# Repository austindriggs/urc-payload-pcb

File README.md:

# Payload PCB at WVU for Mars Society's University Rover Challenge (URC)

## SUMMARY

The Payload PCB serves as an all-purpose control and interface board that contains the Raspberry Pi Pico (RP2040) designed to manage mission-critical sensors and electronics and communicate that information through its Micro USB connector to the LattePanda Sigma SBC.

Learn how to [contribute](CONTRIBUTING.md) (with pictures) to this project.

## FEATURES

- Resettable PTC fuse and reverse voltage protection on +12V Molex Micro-Fit input.
- LTC2990 Quad I2C Voltage, Current, and Temperature Monitor.
- Traco TSR 2 Series +5V and +3V3 regulators: 96% eff, no heat sink required, built in filter caps, and short circuit protection.
- Outputs +12V, +5V, and +3V3 on Molex Micro-Fit.
- Status and error LEDs.
- Connections for both the Pico and an external device to CAN bus.
- 4x STEMMA QT / QWIIC connectors for COTS modules and peripherals.
- 2x custom expansion modules on two 6 pin 0.1" connectors each.
- 4x servo (PWM) outputs on Molex PicoBlades.
- 3x analog inputs on Molex Picoblades.
- 2x digital outputs for relays.
- 2x digital inputs (active-low) for limit switches on manipulator linear rail.
- Micro USB port with soft start to connect to Seeeduino XIAO on manipulator.

## DESIGN

<!--
### SCHEMATIC

TODO

### LAYOUT
--->

<!--
### MODEL

TODO
--->

## DEIMOS (ROVER) AND PHOBOS (DRONE) FOR 2026

Click the image below to watch the System Acceptance Review (SAR) on YouTube:  

## LICENSE

This project is published under the MIT [license](LICENSE).

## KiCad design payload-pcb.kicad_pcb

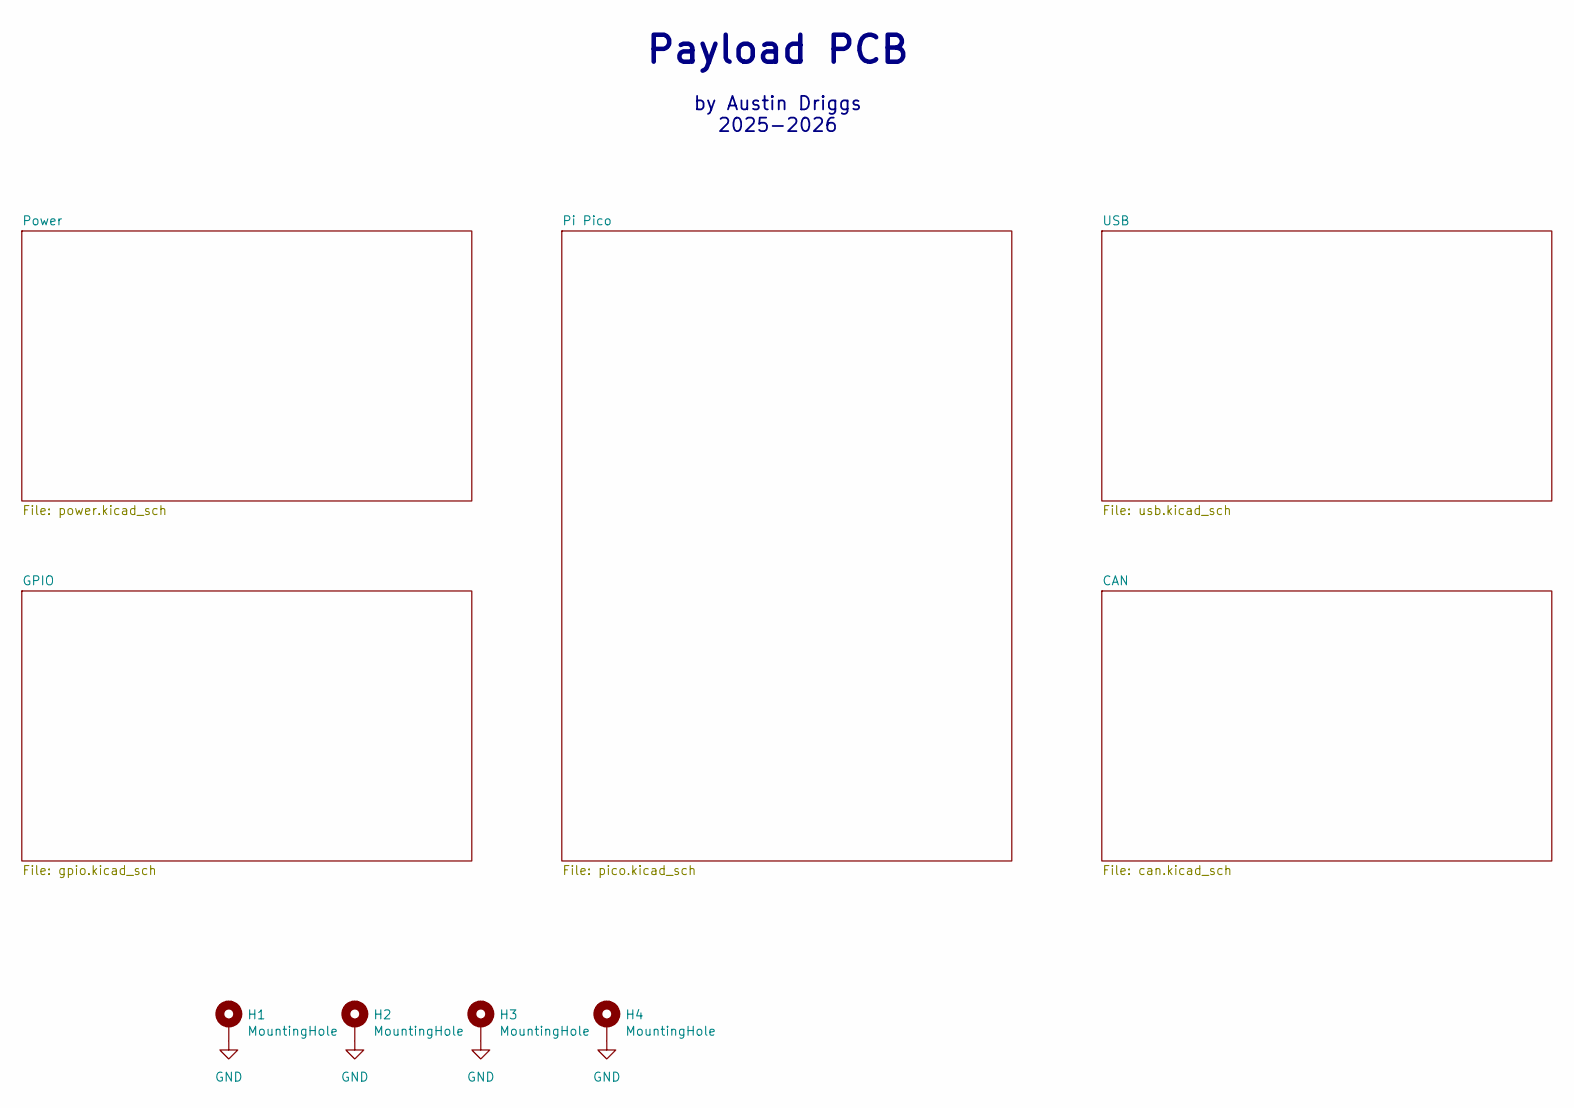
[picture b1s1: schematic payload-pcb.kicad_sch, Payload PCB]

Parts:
H1, H2, H3, H4: MountingHole; MountingHole_3.2mm_M3_DIN965_Pad

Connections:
GND: H1.1, H2.1, H3.1, H4.1; also elsewhere on the board

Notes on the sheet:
Payload PCB
by Austin Driggs 2025-2026

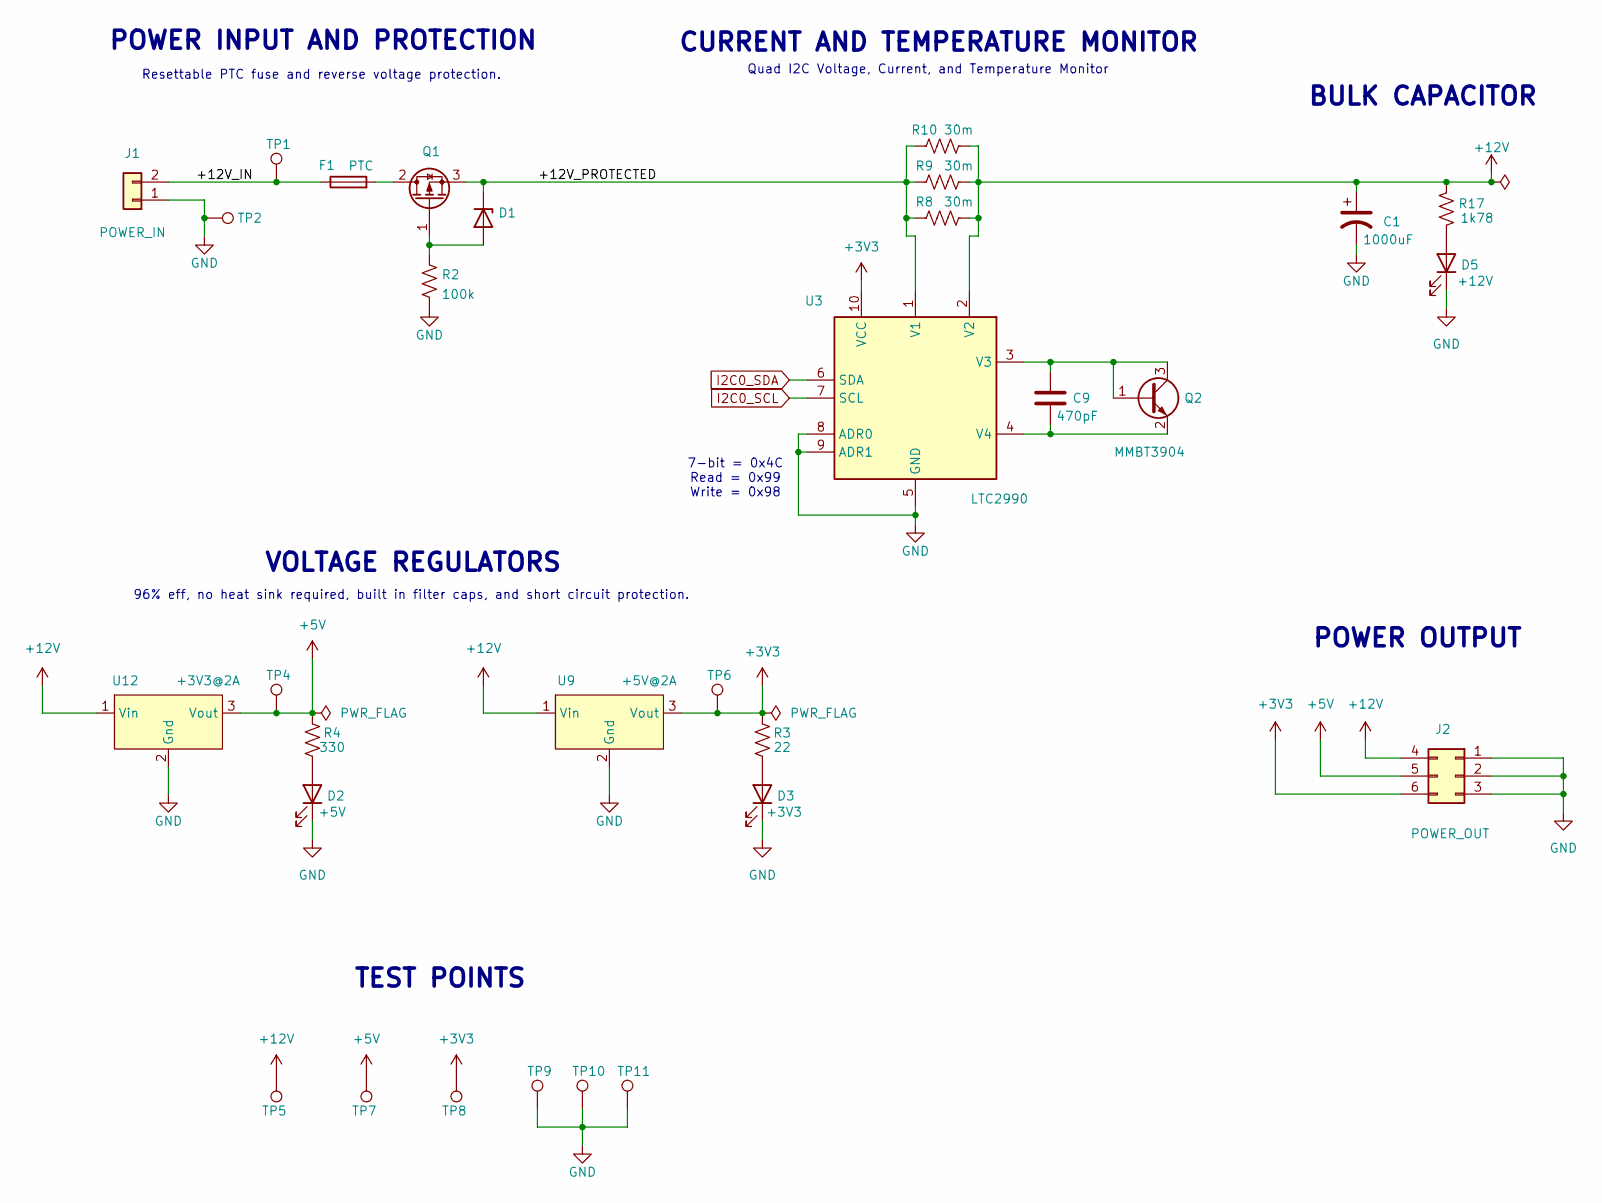
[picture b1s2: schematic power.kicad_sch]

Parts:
C1: 1000uF; CP_Radial_D10.0mm_P5.00mm; Manufacturer Part Number UVR1E102MPD
C9: 470pF; C_0603_1608Metric_Pad1.08x0.95mm_HandSolder; Manufacturer Part Number C0603C471K5RACTU
D1: BZT52C10-TP; D_SOD-123; Manufacturer Part Number BZT52C10-TP
D2: +5V; LED_0805_2012Metric_Pad1.15x1.40mm_HandSolder; Manufacturer Part Number 150080GS75000
D3: +3V3; LED_0805_2012Metric_Pad1.15x1.40mm_HandSolder; Manufacturer Part Number 150080GS75000
D5: +12V; LED_0805_2012Metric_Pad1.15x1.40mm_HandSolder; Manufacturer Part Number 150080GS75000
F1: PTC; Fuse_1210_3225Metric; Manufacturer Part Number 1210L150/16WR
J1: POWER_IN; Molex_Micro-Fit_3.0_43045-0200_2x01_P3.00mm_Horizontal; Manufacturer Part Number 0430450200
J2: POWER_OUT; Molex_Micro-Fit_3.0_43045-0600_2x03_P3.00mm_Horizontal; Manufacturer Part Number 0430450602
Q1: SUD50P10-43L-GE3; TO-252-2; Manufacturer Part Number SUD50P10-43L-GE3
Q2: MMBT3904; SOT-23; Manufacturer Part Number MMBT3904LT1G
R2: 100k; R_0603_1608Metric_Pad0.98x0.95mm_HandSolder; Manufacturer Part Number RMCF0603FT100K
R3: 22; R_0603_1608Metric_Pad0.98x0.95mm_HandSolder; Manufacturer Part Number RNCP0603FTD22R1
R4: 330; R_0603_1608Metric_Pad0.98x0.95mm_HandSolder; Manufacturer Part Number RNCP0603FTD332R
R8, R9, R10: 30m; R_1206_3216Metric_Pad1.30x1.75mm_HandSolder; Manufacturer Part Number CSR1206FT30L0
R17: 1k78; R_0603_1608Metric_Pad0.98x0.95mm_HandSolder; Manufacturer Part Number RNCP0603FTD1K78
TP1: +12V_IN; TestPoint_Pad_D2.0mm
TP2, TP9, TP10, TP11: GND; TestPoint_Pad_D2.0mm
TP4, TP7: +5V; TestPoint_Pad_D2.0mm
TP5: +12V; TestPoint_Pad_D2.0mm
TP6, TP8: +3V3; TestPoint_Pad_D2.0mm
U3: LTC2990; MSOP-10_3x3mm_P0.5mm; Manufacturer Part Number LTC2990IMS#TRPBF
U9: +5V@2A; TSR_2-24xx; Manufacturer Part Number TSR 2-2450
U12: +3V3@2A; TSR_2-24xx; Manufacturer Part Number TSR 2-2433

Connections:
+3V3: J2.6, R3.2, TP6.1, TP8.1, U3.10 (VCC), U9.3 (Vout); also elsewhere on the board
+5V: J2.5, R4.2, TP4.1, TP7.1, U12.3 (Vout); also elsewhere on the board
+12V: C1.1, J2.4, R8.2, R9.2, R10.2, R17.2, TP5.1, U3.2 (V2), U9.1 (Vin), U12.1 (Vin)
/Power/+12V_IN: F1.1, J1.2, TP1.1
/Power/+12V_PROTECTED: D1.1 (K), Q1.3 (S), R8.1, R9.1, R10.1, U3.1 (V1)
GND: C1.2, D2.1 (K), D3.1 (K), D5.1 (K), J1.1, J2.1, J2.2, J2.3, R2.2, TP2.1, TP9.1, TP10.1, TP11.1, U3.5 (GND), U3.8 (ADR0), U3.9 (ADR1), U9.2 (Gnd), U12.2 (Gnd); also elsewhere on the board
I2C0_SCL: U3.7 (SCL); also elsewhere on the board
I2C0_SDA: U3.6 (SDA); also elsewhere on the board
unnamed: D1.2 (A), Q1.1 (G), R2.1
unnamed: D2.2 (A), R4.1
unnamed: D3.2 (A), R3.1
unnamed: D5.2 (A), R17.1
unnamed: F1.2, Q1.2 (D)
unnamed: C9.2, Q2.1 (B), Q2.3 (C), U3.3 (V3)
unnamed: C9.1, Q2.2 (E), U3.4 (V4)

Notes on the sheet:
96% eff, no heat sink required, built in filter caps, and short circuit protection.
CURRENT AND TEMPERATURE MONITOR
BULK CAPACITOR
VOLTAGE REGULATORS
Resettable PTC fuse and reverse voltage protection.
TEST POINTS
POWER OUTPUT
7-bit = 0x4C Read = 0x99 Write = 0x98
POWER INPUT AND PROTECTION
Quad I2C Voltage, Current, and Temperature Monitor

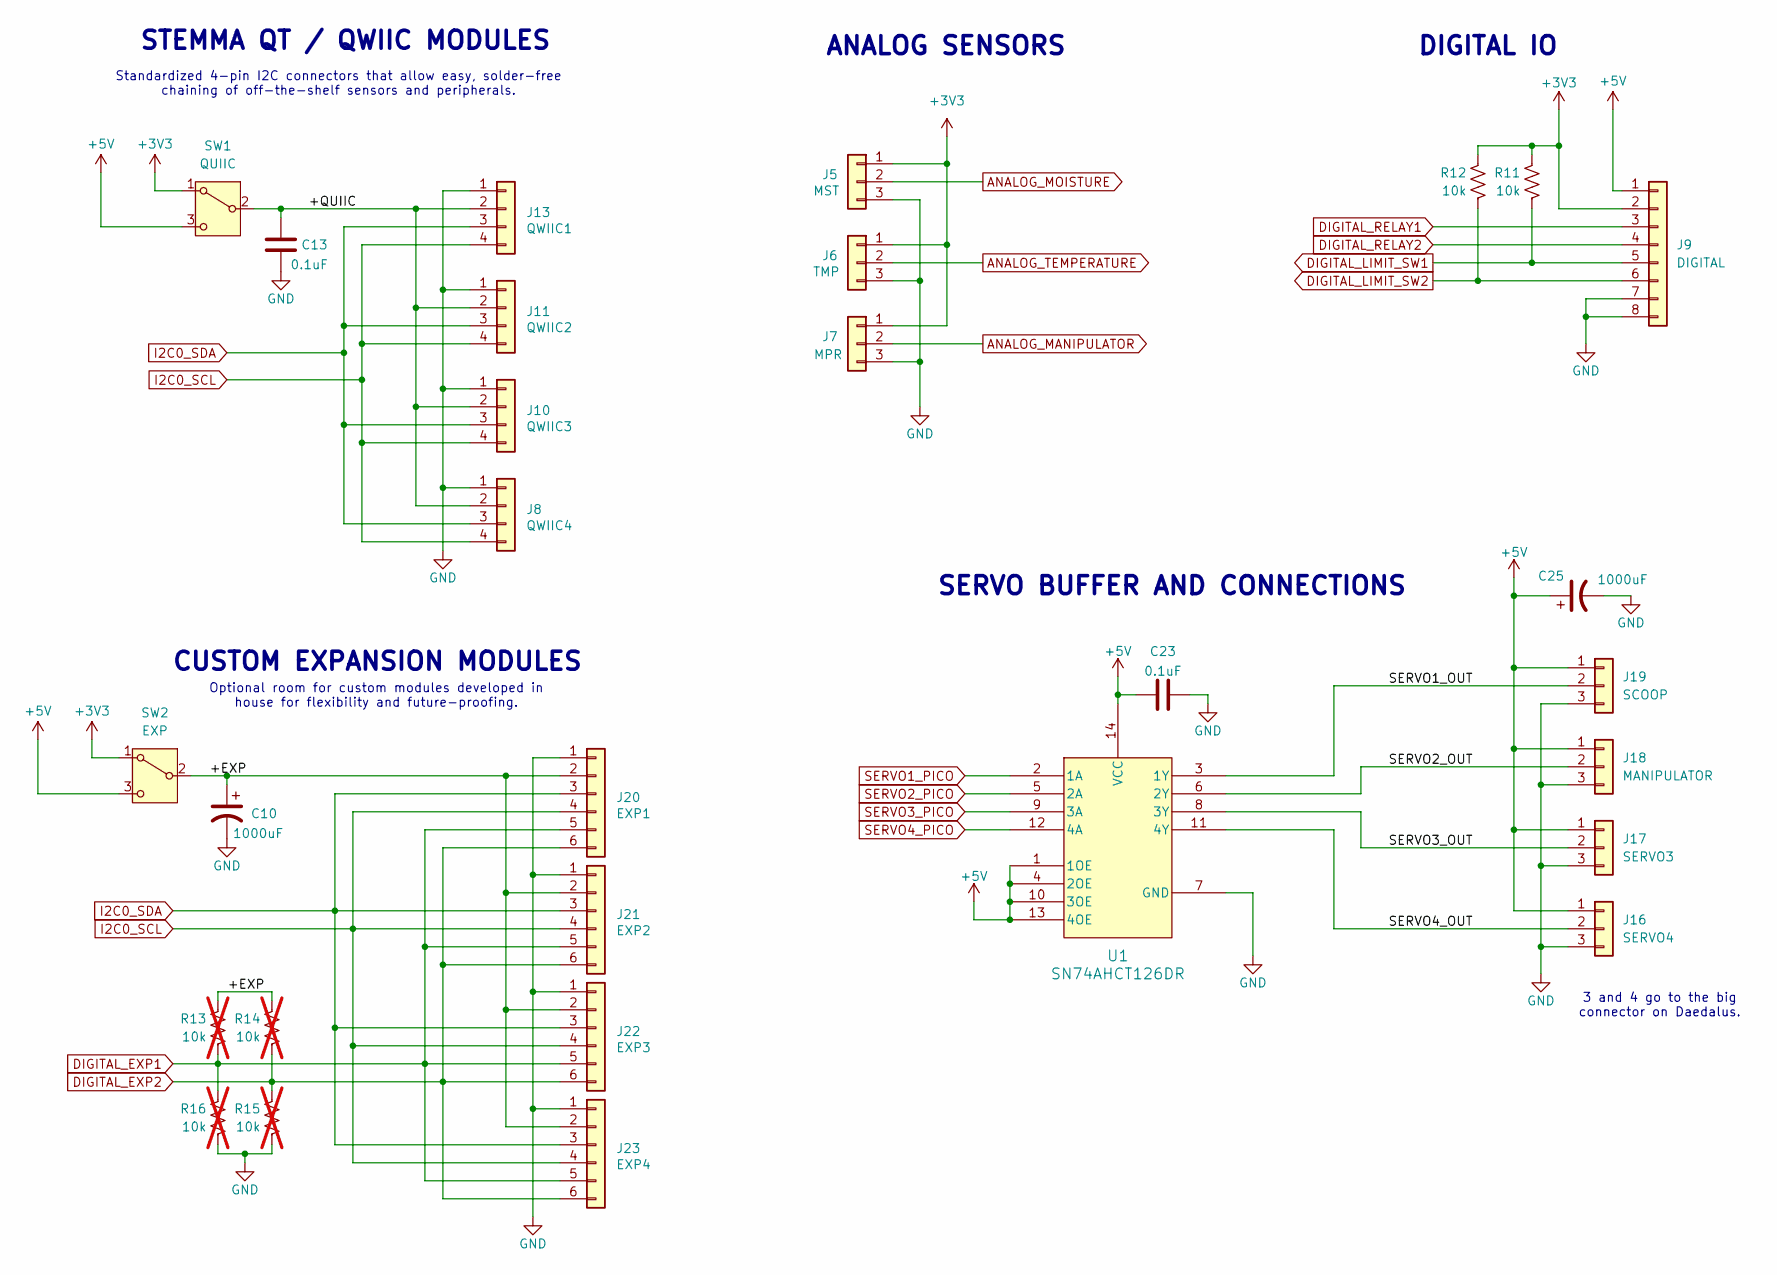
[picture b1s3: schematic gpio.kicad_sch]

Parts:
C10, C25: 1000uF; CP_Radial_D10.0mm_P5.00mm; Manufacturer Part Number UVR1E102MPD
C13, C23: 0.1uF; C_1206_3216Metric_Pad1.33x1.80mm_HandSolder; Manufacturer Part Number C1206C104J5RACTU
J5: MST; Molex_PicoBlade_53047-0310_1x03_P1.25mm_Vertical; Manufacturer Part Number 0530470310
J6: TMP; Molex_PicoBlade_53047-0310_1x03_P1.25mm_Vertical; Manufacturer Part Number 0530470310
J7: MPR; Molex_PicoBlade_53047-0310_1x03_P1.25mm_Vertical; Manufacturer Part Number 0530470310
J8: QWIIC4; JST_GH_BM04B-GHS-TBT_1x04-1MP_P1.25mm_Vertical; Manufacturer Part Number SM04B-GHS-TB
J9: DIGITAL; Molex_PicoBlade_53047-0810_1x08_P1.25mm_Vertical; Manufacturer Part Number 0530470810
J10: QWIIC3; JST_GH_BM04B-GHS-TBT_1x04-1MP_P1.25mm_Vertical; Manufacturer Part Number SM04B-GHS-TB
J11: QWIIC2; JST_GH_BM04B-GHS-TBT_1x04-1MP_P1.25mm_Vertical; Manufacturer Part Number SM04B-GHS-TB
J13: QWIIC1; JST_GH_BM04B-GHS-TBT_1x04-1MP_P1.25mm_Vertical; Manufacturer Part Number SM04B-GHS-TB
J16: SERVO4; Molex_PicoBlade_53047-0310_1x03_P1.25mm_Vertical; Manufacturer Part Number 0530470310
J17: SERVO3; Molex_PicoBlade_53047-0310_1x03_P1.25mm_Vertical; Manufacturer Part Number 0530470310
J18: MANIPULATOR; Molex_PicoBlade_53047-0310_1x03_P1.25mm_Vertical; Manufacturer Part Number 0530470310
J19: SCOOP; Molex_PicoBlade_53047-0310_1x03_P1.25mm_Vertical; Manufacturer Part Number 0530470310
J20: EXP1; PinSocket_1x06_P2.54mm_Vertical; Manufacturer Part Number SSW-106-01-F-S
J21: EXP2; PinSocket_1x06_P2.54mm_Vertical; Manufacturer Part Number SSW-106-01-F-S
J22: EXP3; PinSocket_1x06_P2.54mm_Vertical; Manufacturer Part Number SSW-106-01-F-S
J23: EXP4; PinSocket_1x06_P2.54mm_Vertical; Manufacturer Part Number SSW-106-01-F-S
R11, R12: 10k; R_0603_1608Metric_Pad0.98x0.95mm_HandSolder; Manufacturer Part Number RNCP0603FTD10K0
R13, R14, R15, R16: 10k; R_0603_1608Metric_Pad0.98x0.95mm_HandSolder; Manufacturer Part Number RNCP0603FTD10K0; not fitted
SW1: QUIIC; SW_E-Switch_EG1271_SPDT; Manufacturer Part Number EG1271A
SW2: EXP; SW_E-Switch_EG1271_SPDT; Manufacturer Part Number EG1271A
U1: SN74AHCT126DR; SOIC-14_3.9x8.7mm_P1.27mm; Manufacturer Part Number SN74AHCT126DR

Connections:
+3V3: J5.1, J6.1, J7.1, J9.2, R11.2, R12.2, SW1.1 (A), SW2.1 (A); also elsewhere on the board
+5V: C23.1, C25.1, J9.1, J16.1, J17.1, J18.1, J19.1, SW1.3 (C), SW2.3 (C), U1.1 (1OE), U1.4 (2OE), U1.10 (3OE), U1.13 (4OE), U1.14 (VCC); also elsewhere on the board
/GPIO/+EXP: C10.1, J20.2, J21.2, J22.2, J23.2, R13.2, R14.2, SW2.2 (B)
/GPIO/+QUIIC: C13.2, J8.2, J10.2, J11.2, J13.2, SW1.2 (B)
/GPIO/SERVO1_OUT: J19.2, U1.3 (1Y)
/GPIO/SERVO2_OUT: J18.2, U1.6 (2Y)
/GPIO/SERVO3_OUT: J17.2, U1.8 (3Y)
/GPIO/SERVO4_OUT: J16.2, U1.11 (4Y)
ANALOG_MANIPULATOR: J7.2; also elsewhere on the board
ANALOG_MOISTURE: J5.2; also elsewhere on the board
ANALOG_TEMPERATURE: J6.2; also elsewhere on the board
DIGITAL_EXP1: J20.5, J21.5, J22.5, J23.5, R13.1, R16.2; also elsewhere on the board
DIGITAL_EXP2: J20.6, J21.6, J22.6, J23.6, R14.1, R15.2; also elsewhere on the board
DIGITAL_LIMIT_SW1: J9.5, R11.1; also elsewhere on the board
DIGITAL_LIMIT_SW2: J9.6, R12.1; also elsewhere on the board
DIGITAL_RELAY1: J9.3; also elsewhere on the board
DIGITAL_RELAY2: J9.4; also elsewhere on the board
GND: C10.2, C13.1, C23.2, C25.2, J5.3, J6.3, J7.3, J8.1, J9.7, J9.8, J10.1, J11.1, J13.1, J16.3, J17.3, J18.3, J19.3, J20.1, J21.1, J22.1, J23.1, R15.1, R16.1, U1.7 (GND); also elsewhere on the board
I2C0_SCL: J8.4, J10.4, J11.4, J13.4, J20.4, J21.4, J22.4, J23.4; also elsewhere on the board
I2C0_SDA: J8.3, J10.3, J11.3, J13.3, J20.3, J21.3, J22.3, J23.3; also elsewhere on the board
SERVO1_PICO: U1.2 (1A); also elsewhere on the board
SERVO2_PICO: U1.5 (2A); also elsewhere on the board
SERVO3_PICO: U1.9 (3A); also elsewhere on the board
SERVO4_PICO: U1.12 (4A); also elsewhere on the board

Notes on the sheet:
STEMMA QT / QWIIC MODULES
3 and 4 go to the big connector on Daedalus.
CUSTOM EXPANSION MODULES
Standardized 4-pin I2C connectors that allow easy, solder-free chaining of off-the-shelf sensors and peripherals.
ANALOG SENSORS
SERVO BUFFER AND CONNECTIONS
Optional room for custom modules developed in house for flexibility and future-proofing.
DIGITAL IO

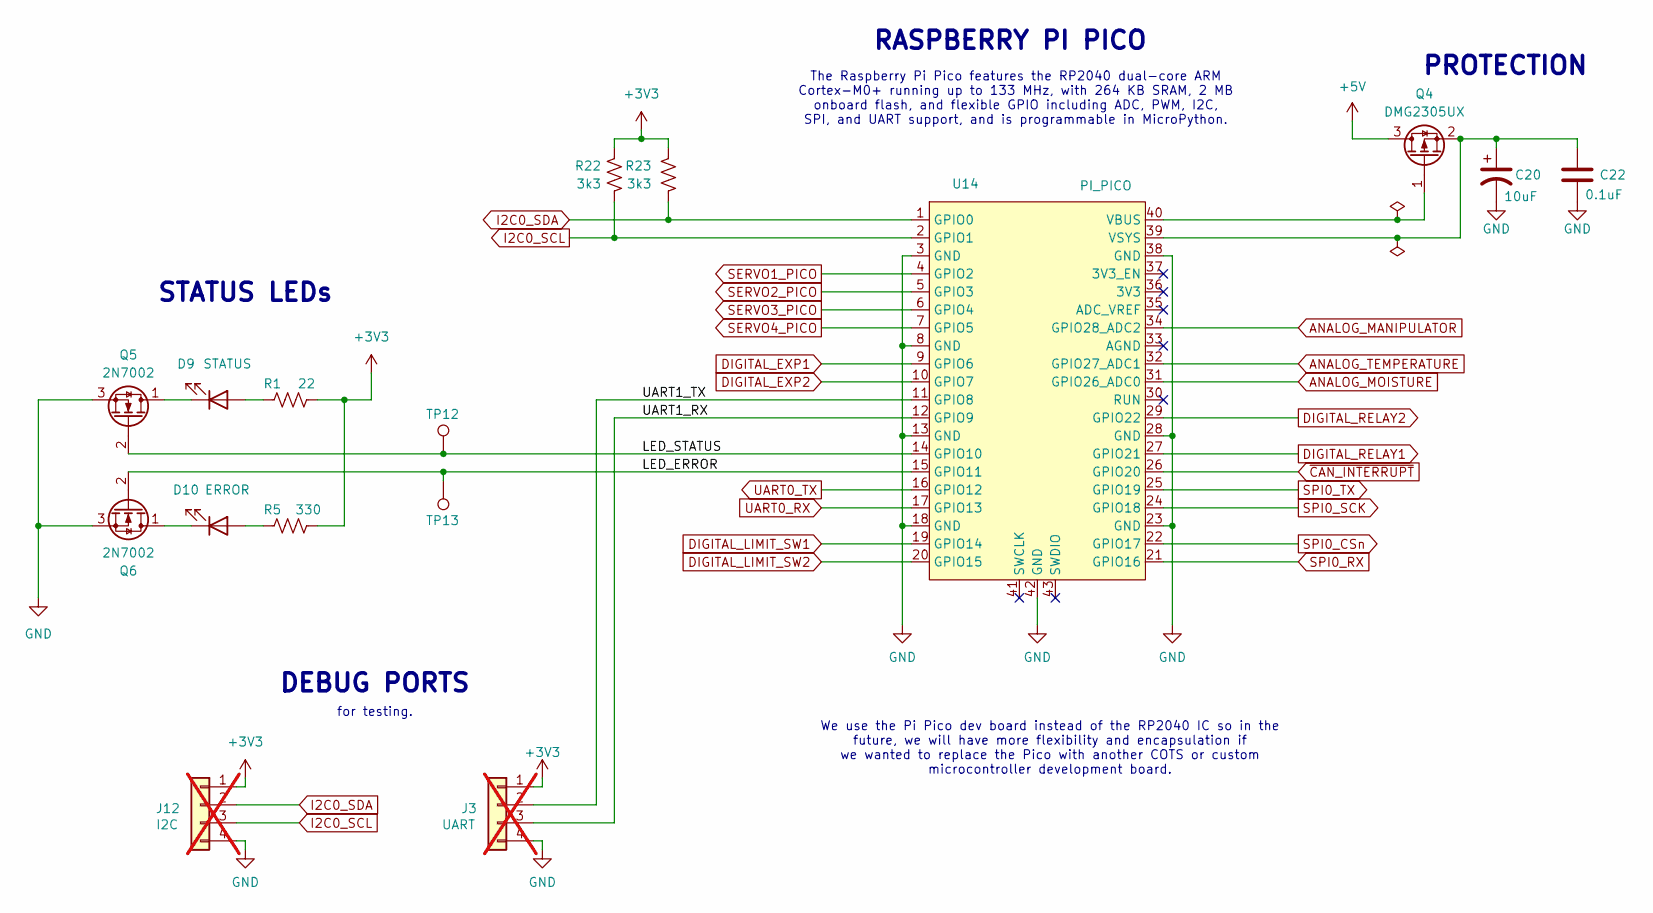
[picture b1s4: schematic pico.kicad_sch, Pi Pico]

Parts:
C20: 10uF; CP_Radial_D8.0mm_P2.50mm; Manufacturer Part Number UVR2C100MPD1TD
C22: 0.1uF; C_1206_3216Metric_Pad1.33x1.80mm_HandSolder; Manufacturer Part Number C1206C104J5RACTU
D9: STATUS; LED_0805_2012Metric_Pad1.15x1.40mm_HandSolder; Manufacturer Part Number 150080BS75000
D10: ERROR; LED_0805_2012Metric_Pad1.15x1.40mm_HandSolder; Manufacturer Part Number 150080RS75000
J3: UART; Molex_PicoBlade_53047-0410_1x04_P1.25mm_Vertical; Manufacturer Part Number 0530470410; not fitted
J12: I2C; Molex_PicoBlade_53047-0410_1x04_P1.25mm_Vertical; Manufacturer Part Number 0530470410; not fitted
Q4: DMG2305UX; SOT-23; Manufacturer Part Number DMG2305UX-7
Q5, Q6: 2N7002; TSOT-23; Manufacturer Part Number 2N7002
R1: 22; R_0603_1608Metric_Pad0.98x0.95mm_HandSolder; Manufacturer Part Number RNCP0603FTD22R1
R5: 330; R_0603_1608Metric_Pad0.98x0.95mm_HandSolder; Manufacturer Part Number RNCP0603FTD332R
R22, R23: 3k3; R_0603_1608Metric_Pad0.98x0.95mm_HandSolder; Manufacturer Part Number RNCP0603FTD3K30
TP12: LED1; TestPoint_Pad_D1.0mm
TP13: LED2; TestPoint_Pad_D1.0mm
U14: PI_PICO; RPi_Pico_SMD_TH; Manufacturer Part Number SC0915

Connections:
+3V3: J3.1, J12.1, R1.2, R5.1, R22.2, R23.2; also elsewhere on the board
+5V: Q4.3 (D); also elsewhere on the board
/Pi Pico/LED_ERROR: Q6.2 (G), TP13.1, U14.15 (GPIO11)
/Pi Pico/LED_STATUS: Q5.2 (G), TP12.1, U14.14 (GPIO10)
/Pi Pico/UART1_RX: J3.3, U14.12 (GPIO9)
/Pi Pico/UART1_TX: J3.2, U14.11 (GPIO8)
ANALOG_MANIPULATOR: U14.34 (GPIO28_ADC2); also elsewhere on the board
ANALOG_MOISTURE: U14.31 (GPIO26_ADC0); also elsewhere on the board
ANALOG_TEMPERATURE: U14.32 (GPIO27_ADC1); also elsewhere on the board
DIGITAL_EXP1: U14.9 (GPIO6); also elsewhere on the board
DIGITAL_EXP2: U14.10 (GPIO7); also elsewhere on the board
DIGITAL_LIMIT_SW1: U14.19 (GPIO14); also elsewhere on the board
DIGITAL_LIMIT_SW2: U14.20 (GPIO15); also elsewhere on the board
DIGITAL_RELAY1: U14.27 (GPIO21); also elsewhere on the board
DIGITAL_RELAY2: U14.29 (GPIO22); also elsewhere on the board
GND: C20.2, C22.1, J3.4, J12.4, Q5.3 (S), Q6.3 (S), U14.3 (GND), U14.8 (GND), U14.13 (GND), U14.18 (GND), U14.23 (GND), U14.28 (GND), U14.38 (GND), U14.42 (GND); also elsewhere on the board
I2C0_SCL: J12.3, R22.1, U14.2 (GPIO1); also elsewhere on the board
I2C0_SDA: J12.2, R23.1, U14.1 (GPIO0); also elsewhere on the board
unnamed: D9.2 (A), R1.1
unnamed: D9.1 (K), Q5.1 (D)
unnamed: D10.2 (A), R5.2
unnamed: D10.1 (K), Q6.1 (D)
unnamed: Q4.1 (G), U14.40 (VBUS)
unnamed: C20.1, C22.2, Q4.2 (S), U14.39 (VSYS)
SERVO1_PICO: U14.4 (GPIO2); also elsewhere on the board
SERVO2_PICO: U14.5 (GPIO3); also elsewhere on the board
SERVO3_PICO: U14.6 (GPIO4); also elsewhere on the board
SERVO4_PICO: U14.7 (GPIO5); also elsewhere on the board
SPI0_CSn: U14.22 (GPIO17); also elsewhere on the board
SPI0_RX: U14.21 (GPIO16); also elsewhere on the board
SPI0_SCK: U14.24 (GPIO18); also elsewhere on the board
SPI0_TX: U14.25 (GPIO19); also elsewhere on the board
UART0_RX: U14.17 (GPIO13); also elsewhere on the board
UART0_TX: U14.16 (GPIO12); also elsewhere on the board
~CAN_INTERRUPT: U14.26 (GPIO20); also elsewhere on the board

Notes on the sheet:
RASPBERRY PI PICO
PROTECTION
DEBUG PORTS
for testing.
We use the Pi Pico dev board instead of the RP2040 IC so in the future, we will have more flexibility and encapsulation if we wanted to replace the Pico with another COTS or custom microcontroller development board.
The Raspberry Pi Pico features the RP2040 dual-core ARM Cortex-M0+ running up to 133 MHz, with 264 KB SRAM, 2 MB onboard flash, and flexible GPIO including ADC, PWM, I2C, SPI, and UART support, and is programmable in MicroPython.
STATUS LEDs

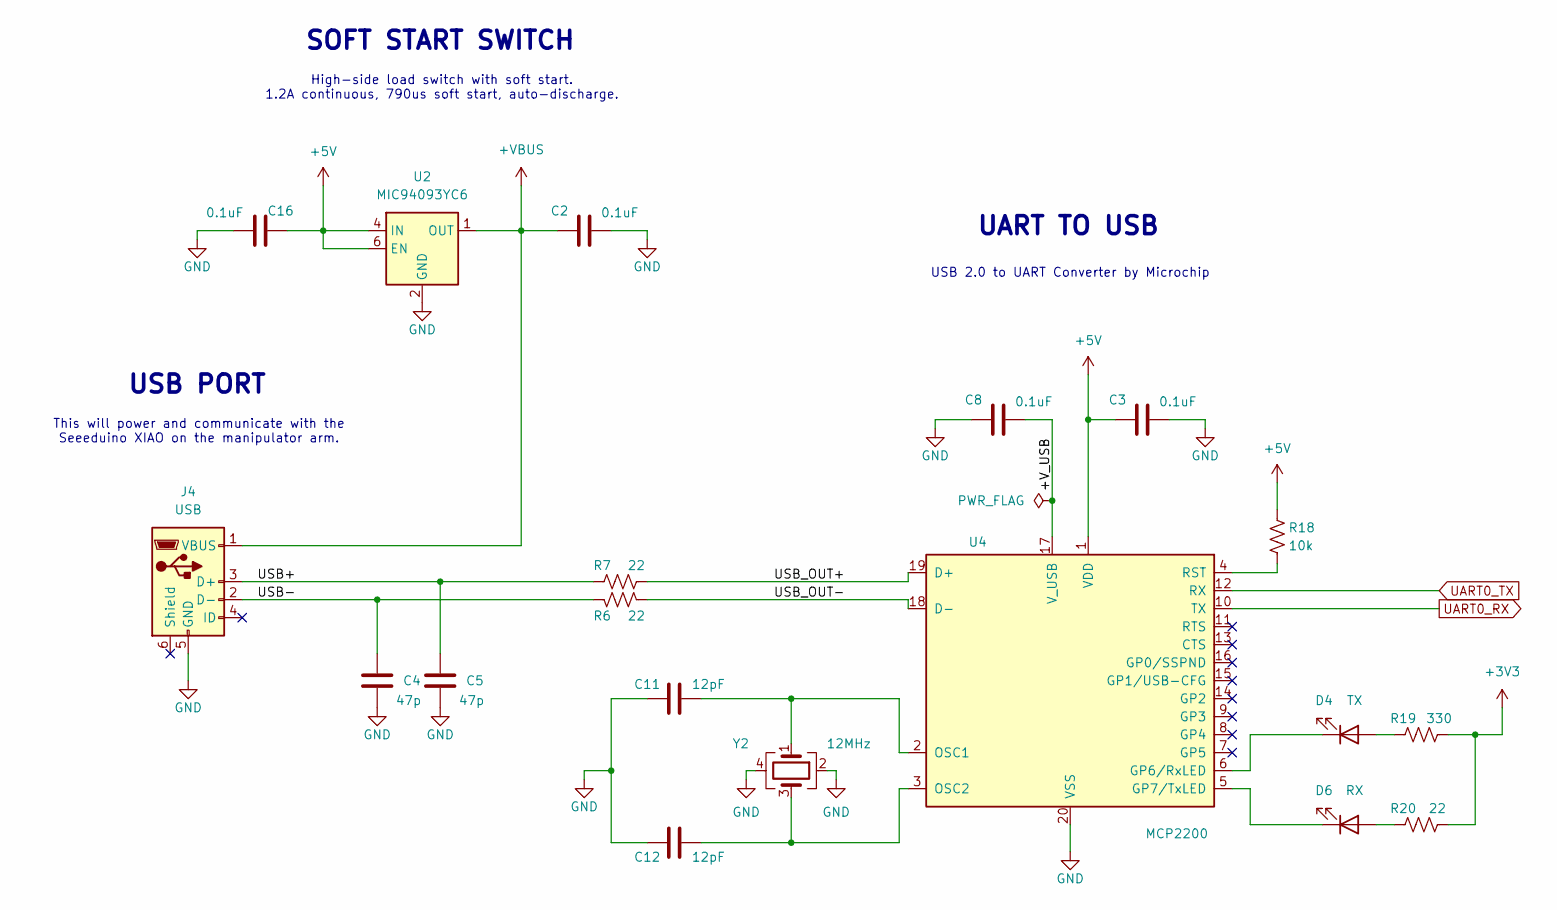
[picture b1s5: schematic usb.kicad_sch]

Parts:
C2, C3, C8, C16: 0.1uF; C_0805_2012Metric_Pad1.18x1.45mm_HandSolder; Manufacturer Part Number C1206C104J5RACTU
C4, C5: 47p; C_0603_1608Metric_Pad1.08x0.95mm_HandSolder; Manufacturer Part Number C0603C470K5RACTU
C11, C12: 12pF; C_0603_1608Metric_Pad1.08x0.95mm_HandSolder; Manufacturer Part Number C0603C120K5RACTU
D4: TX; LED_0805_2012Metric_Pad1.15x1.40mm_HandSolder; Manufacturer Part Number 150080GS75000
D6: RX; LED_0805_2012Metric_Pad1.15x1.40mm_HandSolder; Manufacturer Part Number 150080GS75000
J4: USB; USB_Micro-B_Wuerth_629105150521; Manufacturer Part Number 629105150521
R6, R7, R20: 22; R_0603_1608Metric_Pad0.98x0.95mm_HandSolder; Manufacturer Part Number RNCP0603FTD22R1
R18: 10k; R_0603_1608Metric_Pad0.98x0.95mm_HandSolder; Manufacturer Part Number RNCP0603FTD10K0
R19: 330; R_0603_1608Metric_Pad0.98x0.95mm_HandSolder; Manufacturer Part Number RNCP0603FTD332R
U2: MIC94093YC6; SOT-363_SC-70-6; Manufacturer Part Number MIC94093YC6-TR
U4: MCP2200; SSOP-20_5.3x7.2mm_P0.65mm; Manufacturer Part Number 150-MCP2200T-E/SSCT-ND
Y2: 12MHz; Crystal_SMD_2520-4Pin_2.5x2.0mm; Manufacturer Part Number FH1200004

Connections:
+3V3: R19.1, R20.2; also elsewhere on the board
+5V: C3.2, C16.2, R18.2, U2.4 (IN), U2.6 (EN), U4.1 (VDD); also elsewhere on the board
+VBUS: C2.2, J4.1 (VBUS), U2.1 (OUT)
/USB/+V_USB: C8.1, U4.17 (V_USB)
/USB/USB+: C5.2, J4.3 (D+), R7.1
/USB/USB-: C4.2, J4.2 (D-), R6.1
/USB/USB_OUT+: R7.2, U4.19 (D+)
/USB/USB_OUT-: R6.2, U4.18 (D-)
GND: C2.1, C3.1, C4.1, C5.1, C8.2, C11.1, C12.1, C16.1, J4.5 (GND), U2.2 (GND), U2.5 (GND), U4.20 (VSS), Y2.2, Y2.4; also elsewhere on the board
unnamed: D4.2 (A), R19.2
unnamed: D4.1 (K), U4.6 (GP6/RxLED)
unnamed: D6.2 (A), R20.1
unnamed: D6.1 (K), U4.5 (GP7/TxLED)
unnamed: C11.2, U4.2 (OSC1), Y2.1
unnamed: C12.2, U4.3 (OSC2), Y2.3
unnamed: R18.1, U4.4 (RST)
UART0_RX: U4.10 (TX); also elsewhere on the board
UART0_TX: U4.12 (RX); also elsewhere on the board

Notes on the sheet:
USB PORT
This will power and communicate with the Seeeduino XIAO on the manipulator arm.
SOFT START SWITCH
UART TO USB
High-side load switch with soft start. 1.2A continuous, 790us soft start, auto-discharge.
USB 2.0 to UART Converter by Microchip

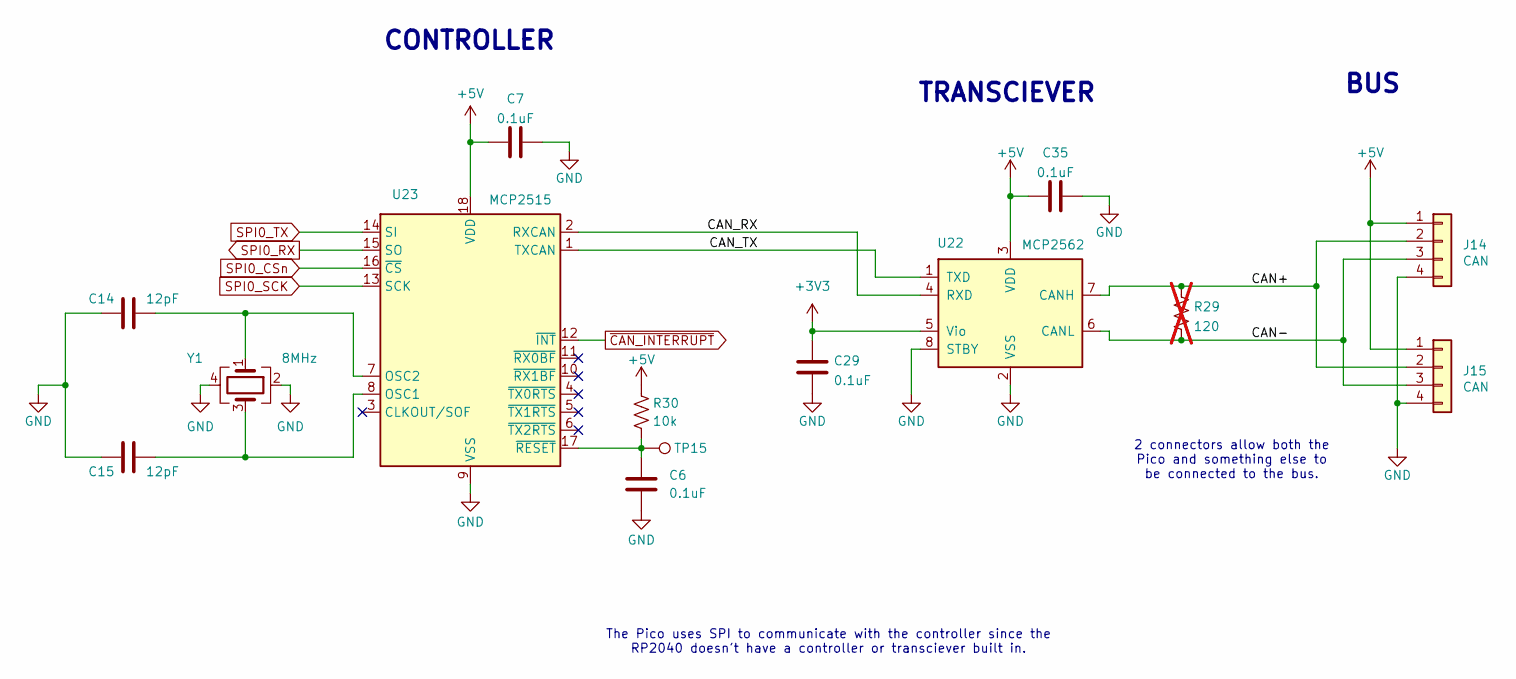
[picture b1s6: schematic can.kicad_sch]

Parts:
C6, C7, C29, C35: 0.1uF; C_1206_3216Metric_Pad1.33x1.80mm_HandSolder; Manufacturer Part Number C1206C104J5RACTU
C14, C15: 12pF; C_0603_1608Metric_Pad1.08x0.95mm_HandSolder; Manufacturer Part Number C0603C120K5RACTU
J14, J15: CAN; Molex_PicoBlade_53047-0410_1x04_P1.25mm_Vertical; Manufacturer Part Number 0530470410
R29: 120; R_0603_1608Metric_Pad0.98x0.95mm_HandSolder; Manufacturer Part Number RNCP0603FTD121R; not fitted
R30: 10k; R_0603_1608Metric_Pad0.98x0.95mm_HandSolder; Manufacturer Part Number RNCP0603FTD10K0
TP15: ~{RST}; TestPoint_Pad_D1.0mm
U22: MCP2562; SOIC-8_3.9x4.9mm_P1.27mm; Manufacturer Part Number MCP2562FDT-E/SN
U23: MCP2515; SOIC-18W_7.5x11.6mm_P1.27mm; Manufacturer Part Number MCP2515T-E/SO
Y1: 8MHz; Crystal_SMD_3225-4Pin_3.2x2.5mm; Manufacturer Part Number FL0800011Q

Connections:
+3V3: C29.1, U22.5 (Vio); also elsewhere on the board
+5V: C7.1, C35.1, J14.1, J15.1, R30.2, U22.3 (VDD), U23.18 (VDD); also elsewhere on the board
/CAN/CAN+: J14.2, J15.2, R29.2, U22.7 (CANH)
/CAN/CAN-: J14.3, J15.3, R29.1, U22.6 (CANL)
/CAN/CAN_RX: U22.4 (RXD), U23.2 (RXCAN)
/CAN/CAN_TX: U22.1 (TXD), U23.1 (TXCAN)
GND: C6.2, C7.2, C14.1, C15.1, C29.2, C35.2, J14.4, J15.4, U22.2 (VSS), U22.8 (STBY), U23.9 (VSS), Y1.2, Y1.4; also elsewhere on the board
unnamed: C15.2, U23.8 (OSC1), Y1.3
unnamed: C14.2, U23.7 (OSC2), Y1.1
unnamed: C6.1, R30.1, TP15.1, U23.17 (~RESET)
SPI0_CSn: U23.16 (~CS); also elsewhere on the board
SPI0_RX: U23.15 (SO); also elsewhere on the board
SPI0_SCK: U23.13 (SCK); also elsewhere on the board
SPI0_TX: U23.14 (SI); also elsewhere on the board
~CAN_INTERRUPT: U23.12 (~INT); also elsewhere on the board

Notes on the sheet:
The Pico uses SPI to communicate with the controller since the RP2040 doesn't have a controller or transciever built in.
2 connectors allow both the Pico and something else to be connected to the bus.
CONTROLLER
BUS
TRANSCIEVER

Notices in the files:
parts and their libraries:
Copyright 2021 Accelerated Designs. All rights reserved.
